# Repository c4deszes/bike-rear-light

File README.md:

# Rear Light

> An integrated tail, brake and turn signal light for bicycles.

## Gen 1

This generation is meant to demonstrate the tail light and brake light capabilities, turn signals
are not present.

The expected takeaways from it are:

- whether this simplified single PCB assembly is robust enough
- whether the amount of light produced is sufficient
- how certain lenses affect the optical qualities 
- what the thermals look like given the power consumption and enclosure with passive cooling
- whether this accelerometer is reliable to be used for the brake lights

Key findings:

- Accelerometer alone is not reliable for brake detection due to road vibrations. With filtering
  the reaction time goes up.
- Linear LED drivers are not efficient for the expected bus voltages, this is a problem for the
  continously on tail light
- Single LEDs spread out on a large area need lots of diffusing which reduces the light output

## Gen 1b

This generation is meant as a patch for the weak and uneven light output of Gen1. It's based on the
Gen1 front light hardware put inside a custom case.

There are no expectations.

Key findings:

- Mounting bracket broke during two incidents in an unservicable way

## Gen 2

This generation is meant to merge the good parts of Gen1 and Gen1b and improve a couple of things.
The main new feature is the included radar and the primary improvements are increased operational
voltage range and additional monitoring.

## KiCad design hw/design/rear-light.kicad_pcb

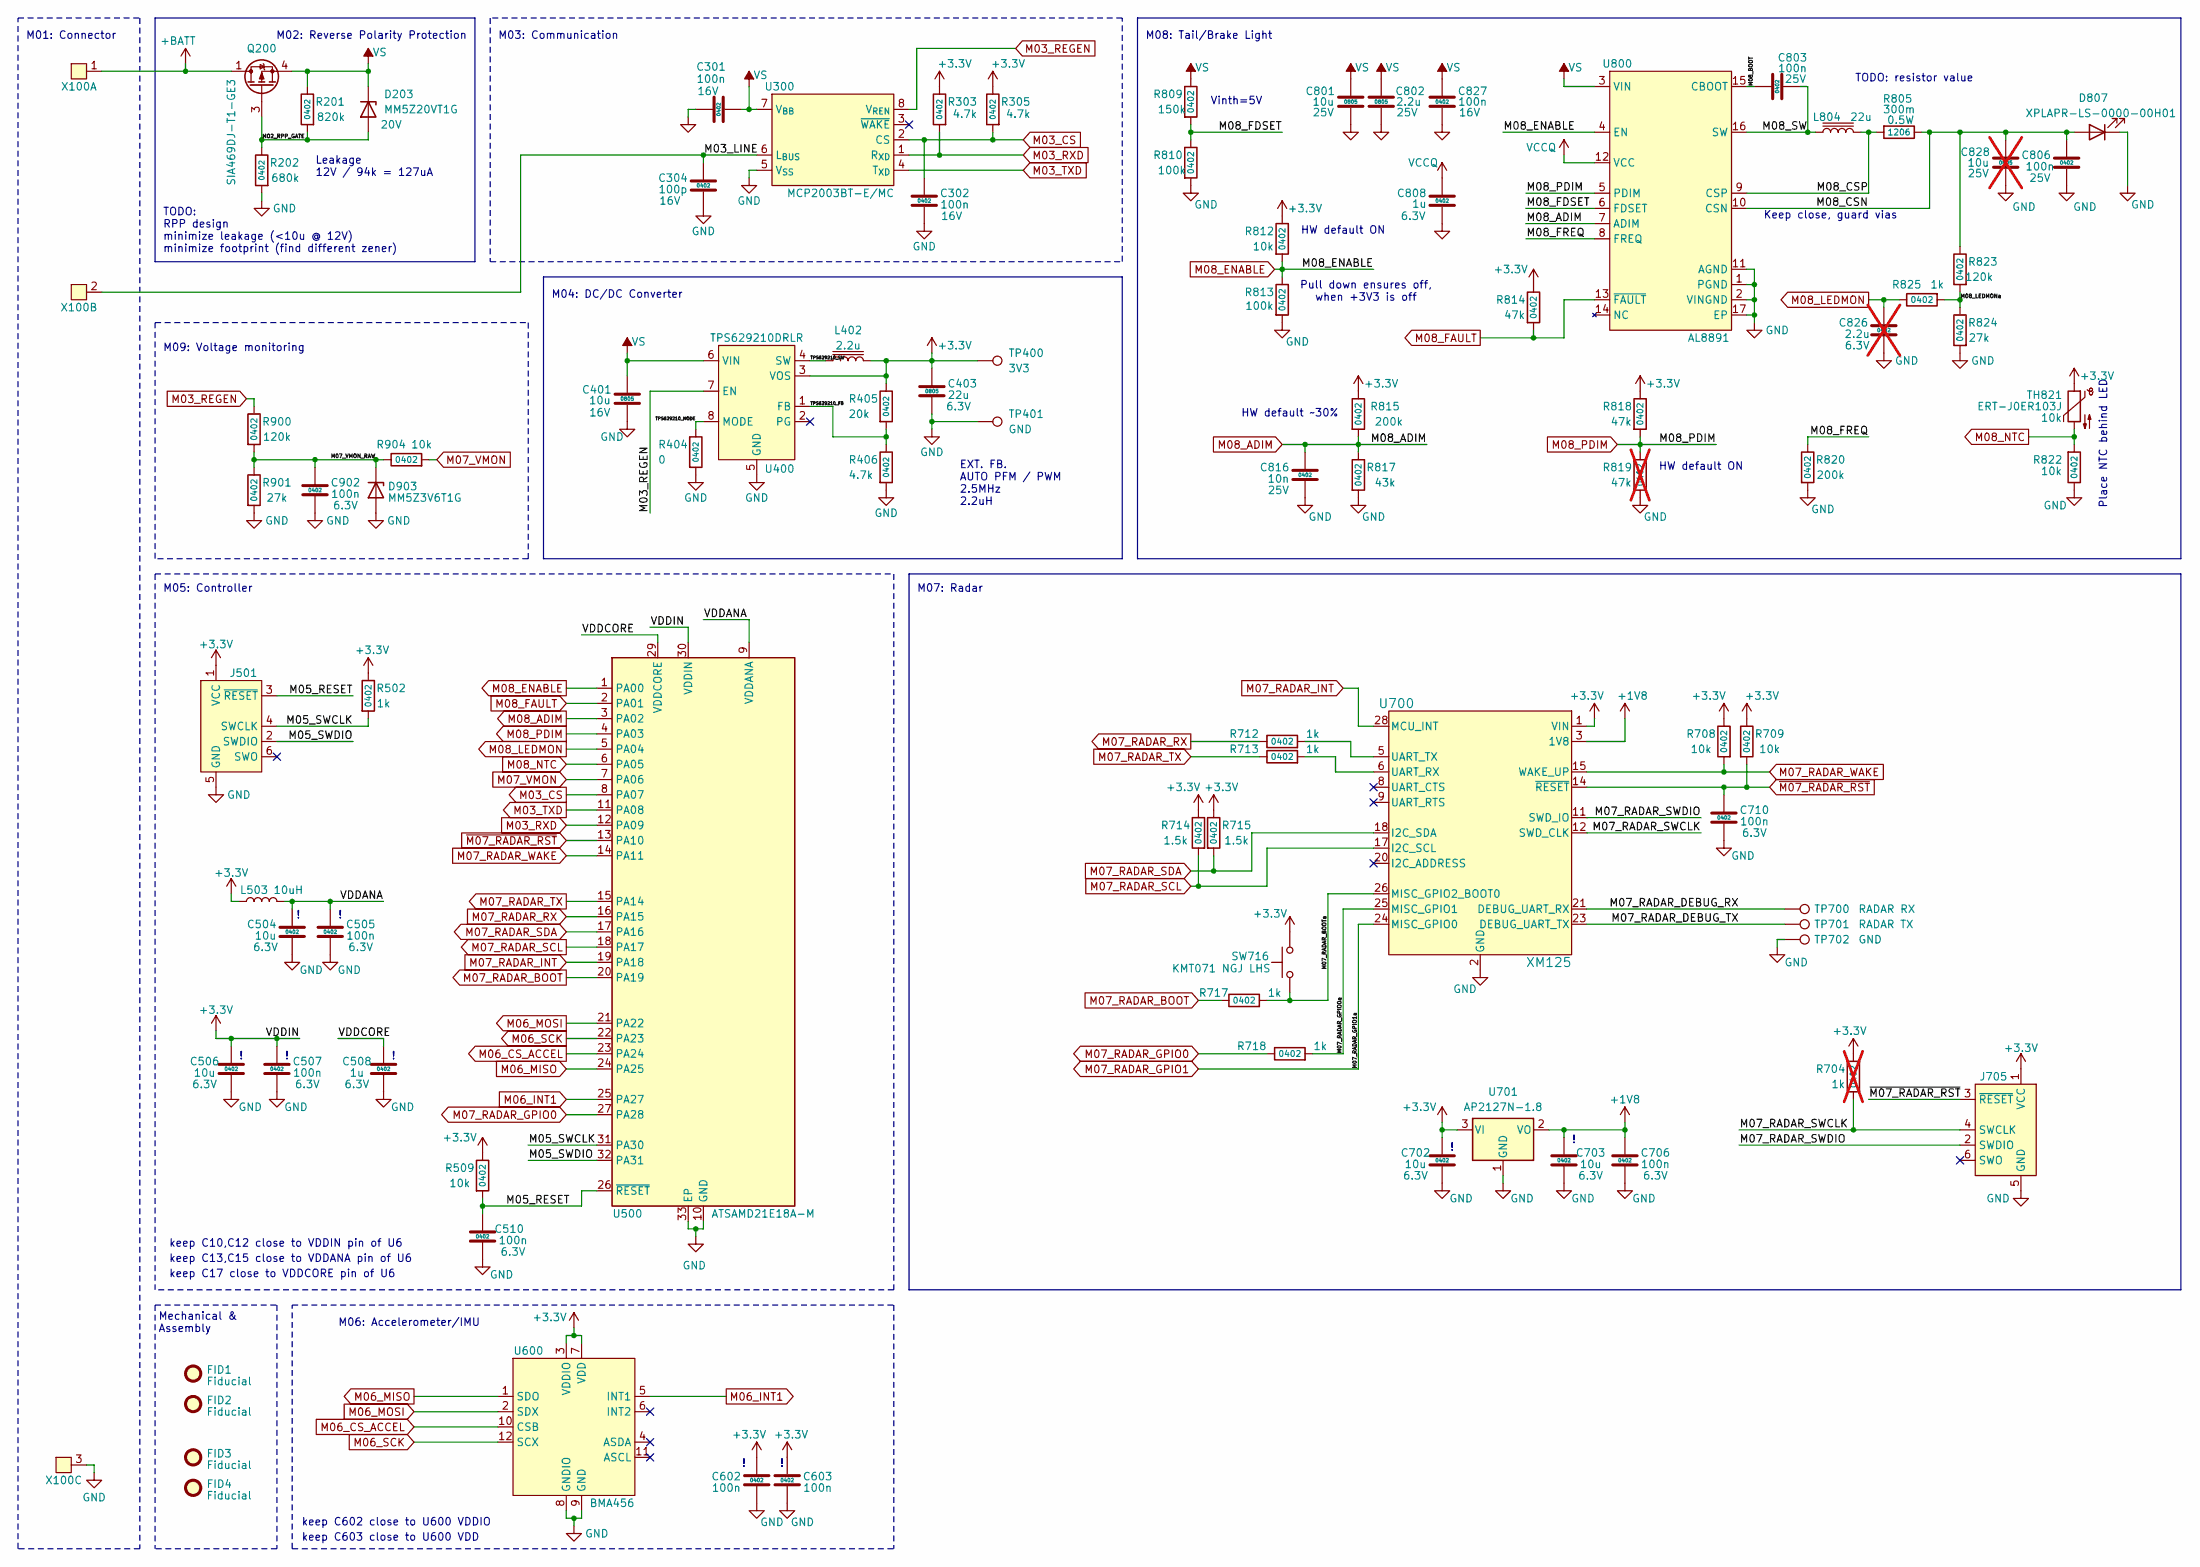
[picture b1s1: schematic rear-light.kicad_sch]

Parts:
C301, C302, C827: 100n; C_0402_1005Metric; Rating 16V
C304: 100p; C_0402_1005Metric; Rating 16V
C401: 10u; C_0805_2012Metric; Rating 16V
C403: 22u; C_0805_2012Metric; Rating 6.3V
C504, C506, C702, C703: 10u; C_0402_1005Metric; Rating 6.3V
C505, C507, C510, C706, C710, C902: 100n; C_0402_1005Metric; Rating 6.3V
C508, C808: 1u; C_0402_1005Metric; Rating 6.3V
C602, C603: 100n; C_0402_1005Metric
C801: 10u; C_0805_2012Metric; Rating 25V
C802: 2.2u; C_0805_2012Metric; Rating 25V
C803: 100n; C_0603_1608Metric; Rating 25V
C806: 100n; C_0402_1005Metric; Rating 25V
C816: 10n; C_0402_1005Metric; Rating 25V
C826: 2.2u; C_0402_1005Metric; Rating 6.3V; not fitted
C828: 10u; C_0805_2012Metric; Rating 25V; not fitted
D203: MM5Z20VT1G; D_SOD-523; Rating 20V
D807: XPLAPR-LS-0000-00H01; LED_Cree-XP
D903: MM5Z3V6T1G; D_SOD-523
FID1, FID2, FID3, FID4: Fiducial; Fiducial_0.5mm_Mask1mm
J501, J705: Conn_ARM_SWD_TagConnect_TC2030-NL; Tag-Connect_TC2030-IDC-NL_2x03_P1.27mm_Vertical
L402: 2.2u; L_Coilcraft_LPS3010
L503: 10uH; L_0603_1608Metric
L804: 22u; ASPI-6045
Q200: SIA469DJ-T1-GE3; Vishay_PowerPAK_SC70-6L_Single
R201: 820k; R_0402_1005Metric
R202: 680k; R_0402_1005Metric
R303, R305, R406: 4.7k; R_0402_1005Metric
R404: 0; R_0402_1005Metric
R405: 20k; R_0402_1005Metric
R502, R712, R713, R717, R718, R825: 1k; R_0402_1005Metric
R509, R708, R709, R812, R822, R904: 10k; R_0402_1005Metric
R704: 1k; R_0402_1005Metric; not fitted
R714, R715: 1.5k; R_0402_1005Metric
R805: 300m; R_1206_3216Metric; Rating 0.5W
R809: 150k; R_0402_1005Metric
R810, R813: 100k; R_0402_1005Metric
R814, R818: 47k; R_0402_1005Metric
R815, R820: 200k; R_0402_1005Metric
R817: 43k; R_0402_1005Metric
R819: 47k; R_0402_1005Metric; not fitted
R823, R900: 120k; R_0402_1005Metric
R824, R901: 27k; R_0402_1005Metric
SW716: KMT071 NGJ LHS; KMT0
TH821: ERT-J0ER103J; R_0402_1005Metric
TP400: 3V3; TestPoint_Pad_D1.0mm
TP401, TP702: GND; TestPoint_Pad_D1.0mm
TP700: RADAR RX; TestPoint_Pad_D1.0mm
TP701: RADAR TX; TestPoint_Pad_D1.0mm
U300: MCP2003BT-E/MC; DFN-8-1EP_3x2mm_P0.5mm_EP1.7x1.4mm
U400: TPS629210DRLR; SOT-583-8
U500: ATSAMD21E18A-M; QFN-32-1EP_5x5mm_P0.5mm_EP3.6x3.6mm
U600: BMA456; LGA-12_2x2mm_P0.5mm
U700: XM125; XM125_ACC-M
U701: AP2127N-1.8; SOT-23
U800: AL8891; TSSOP-16-1EP_4.4x5mm_P0.65mm_EP3x3mm
X100: JST_JWPF_B03B-JWPF-SK-R_1x03_P2.00mm_Vertical

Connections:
+1V8: C703.2, C706.2, U700.3 (1V8), U701.2 (VO)
+3.3V: C403.1, C506.2, C507.2, C602.2, C603.1, C702.2, J501.1 (VCC), J705.1 (VCC), L402.2, L503.1, R303.1, R305.1, R405.1, R502.1, R509.1, R704.1, R708.1, R709.1, R714.1, R715.1, R812.1, R814.1, R815.1, R818.1, SW716.2, TH821.1, TP400.1, U400.3 (VOS), U500.30 (VDDIN), U600.3 (VDDIO), U600.7 (VDD), U700.1 (VIN), U701.3 (VI)
+BATT: Q200.1 (D), X100.1
/M02_RPP_GATE: D203.2 (A), Q200.3 (G), R201.2, R202.1
/M03_LINE: C304.2, U300.6 (L_{BUS}), X100.2
/M05_RESET: C510.2, J501.3 (~RESET), R509.2, U500.26 (~RESET)
/M05_SWCLK: J501.4 (SWCLK), R502.2, U500.31 (PA30)
/M05_SWDIO: J501.2 (SWDIO), U500.32 (PA31)
/M07_RADAR_BOOTa: R717.2, SW716.1, U700.26 (MISC_GPIO2_BOOT0)
/M07_RADAR_DEBUG_RX: TP700.1, U700.21 (DEBUG_UART_RX)
/M07_RADAR_DEBUG_TX: TP701.1, U700.23 (DEBUG_UART_TX)
/M07_RADAR_GPIO0a: R718.2, U700.25 (MISC_GPIO1)
/M07_RADAR_SWCLK: J705.4 (SWCLK), R704.2, U700.12 (SWD_CLK)
/M07_RADAR_SWDIO: J705.2 (SWDIO), U700.11 (SWD_IO)
/M07_VMON_RAW: C902.2, D903.1 (K), R900.2, R901.1, R904.1
/M08_BOOT: C803.1, U800.15 (CBOOT)
/M08_CSN: C806.1, C828.2, D807.2 (A), R805.1, R823.1, U800.10 (CSN)
/M08_CSP: L804.2, R805.2, U800.9 (CSP)
/M08_FDSET: R809.2, R810.1, U800.6 (FDSET)
/M08_FREQ: R820.1, U800.8 (FREQ)
/M08_LEDMONa: R823.2, R824.1, R825.2
/M08_SW: C803.2, L804.1, U800.16 (SW)
/TPS629210_FB: R405.2, R406.1, U400.1 (FB)
/TPS629210_MODE: R404.1, U400.8 (MODE)
/TPS629210_SW: L402.1, U400.4 (SW)
/VDDANA: C504.2, C505.2, L503.2, U500.9 (VDDANA)
/VDDCORE: C508.2, U500.29 (VDDCORE)
GND: C301.1, C302.1, C304.1, C401.1, C403.2, C504.1, C505.1, C506.1, C507.1, C508.1, C510.1, C602.1, C603.2, C702.1, C703.1, C706.1, C710.1, C801.1, C802.1, C806.2, C808.1, C816.2, C826.1, C827.1, C828.1, C902.1, D807.1 (K), D903.2 (A), J501.5 (GND), J705.5 (GND), R202.2, R404.2, R406.2, R810.2, R813.2, R817.2, R819.2, R820.2, R822.1, R824.2, R901.2, TP401.1, TP702.1, U300.5 (V_{SS}), U400.5 (GND), U500.10 (GND), U500.28 (GND), U500.33 (EP), U600.8 (GNDIO), U600.9 (GND), U700.2 (GND), U700.4 (GND), U700.7 (GND), U700.10 (GND), U700.13 (GND), U700.16 (GND), U700.19 (GND), U700.22 (GND), U700.27 (GND), U701.1 (GND), U800.1 (PGND), U800.2 (VINGND), U800.11 (AGND), U800.17 (EP), X100.3
M03_CS: C302.2, R305.2, U300.2 (CS), U500.8 (PA07)
M03_REGEN: R900.1, U300.8 (V_{REN}), U400.7 (EN)
M03_RXD: R303.2, U300.1 (R_{XD}), U500.12 (PA09)
M03_TXD: U300.4 (T_{XD}), U500.11 (PA08)
M06_CS_ACCEL: U500.23 (PA24), U600.10 (CSB)
M06_INT1: U500.25 (PA27), U600.5 (INT1)
M06_MISO: U500.24 (PA25), U600.1 (SDO)
M06_MOSI: U500.21 (PA22), U600.2 (SDX)
M06_SCK: U500.22 (PA23), U600.12 (SCX)
M07_RADAR_BOOT: R717.1, U500.20 (PA19)
M07_RADAR_GPIO0: R718.1, U500.27 (PA28)
M07_RADAR_GPIO1: U700.24 (MISC_GPIO0)
M07_RADAR_INT: U500.19 (PA18), U700.28 (MCU_INT)
M07_RADAR_RX: R712.1, U500.16 (PA15)
M07_RADAR_SCL: R714.2, U500.18 (PA17), U700.17 (I2C_SCL)
M07_RADAR_SDA: R715.2, U500.17 (PA16), U700.18 (I2C_SDA)
M07_RADAR_TX: R713.1, U500.15 (PA14)
M07_RADAR_WAKE: R708.2, U500.14 (PA11), U700.15 (WAKE_UP)
M07_VMON: R904.2, U500.7 (PA06)
M08_ADIM: C816.1, R815.2, R817.1, U500.3 (PA02), U800.7 (ADIM)
M08_ENABLE: R812.2, R813.1, U500.1 (PA00), U800.4 (EN)
M08_FAULT: R814.2, U500.2 (PA01), U800.13 (~FAULT)
M08_LEDMON: C826.2, R825.1, U500.5 (PA04)
M08_NTC: R822.2, TH821.2, U500.6 (PA05)
M08_PDIM: R818.2, R819.1, U500.4 (PA03), U800.5 (PDIM)
unnamed: R713.2, U700.6 (UART_RX)
unnamed: R712.2, U700.5 (UART_TX)
VCCQ: C808.2, U800.12 (VCC)
VS: C301.2, C401.2, C801.2, C802.2, C827.2, D203.1 (K), Q200.4 (S), R201.1, R809.1, U300.7 (V_{BB}), U400.6 (VIN), U800.3 (VIN)
~M07_RADAR_RST: C710.2, J705.3 (~RESET), R709.2, U500.13 (PA10), U700.14 (~RESET)

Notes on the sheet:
M01: Connector
M04: DC/DC Converter
keep C17 close to VDDCORE pin of U6
M05: Controller
HW default ON
keep C13,C15 close to VDDANA pin of U6
Pull down ensures off, when +3V3 is off
EXT. FB. AUTO PFM / PWM 2.5MHz 2.2uH
M08: Tail/Brake Light
M06: Accelerometer/IMU
keep C10,C12 close to VDDIN pin of U6
M07: Radar
M02: Reverse Polarity Protection
keep C602 close to U600 VDDIO
Mechanical & Assembly
HW default ~30%
TODO: resistor value
M03: Communication
TODO: RPP design minimize leakage (<10u @ 12V) minimize footprint (find different zener)
M09: Voltage monitoring
Leakage 12V / 94k = 127uA
Vinth=5V
keep C603 close to U600 VDD
Keep close, guard vias
Place NTC behind LED

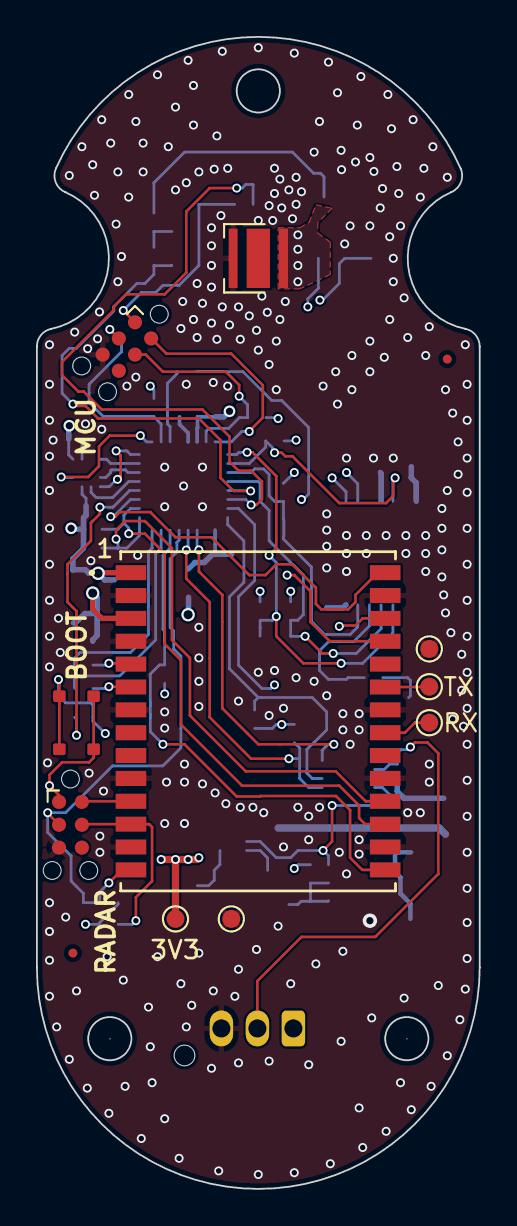
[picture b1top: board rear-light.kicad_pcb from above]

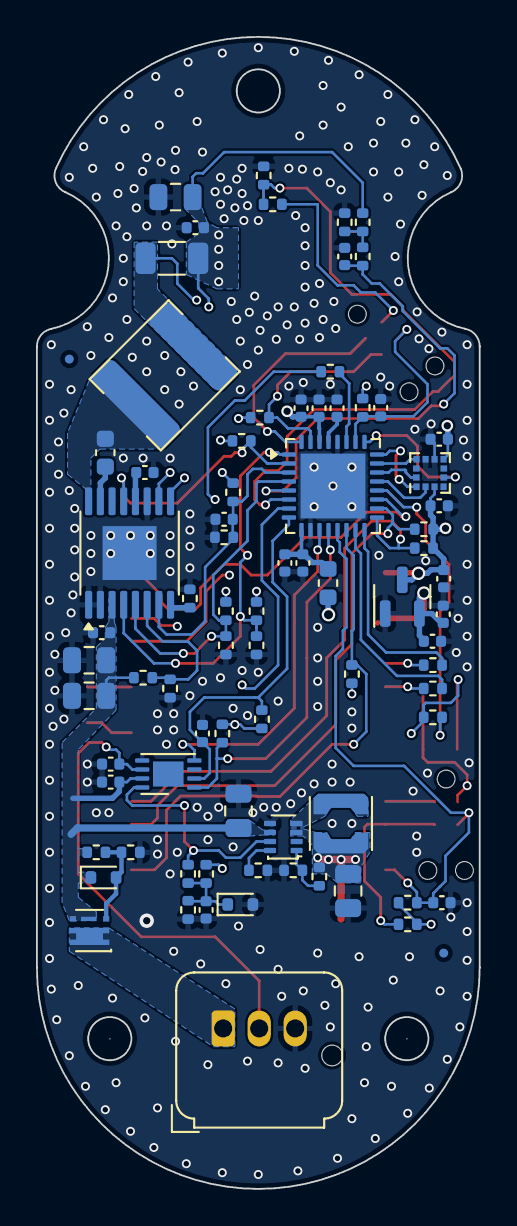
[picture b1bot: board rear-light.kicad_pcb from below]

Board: 4 copper layers, 24.6 x 64.0 mm, 91 parts (79 on the bottom side), 57 nets.

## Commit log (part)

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2024-02-06 Initial system requirements, arch, design
2024-03-10 Updated system design
2024-03-13 Updated system requirements
2024-03-13 Mechanical design Gen1.0
2024-03-14 Hardware design Gen1.0
2024-03-17 Adds hardware workflow
2024-03-17 drawio installation
2024-03-17 Fix CI
2024-03-24 Design updates
    Finalized schematic, layout is unchanged
2024-03-24 Gen1.0 design finalization (#1)
    * Final layout for Gen1.0, PCB has been ordered
    * Design documentation is mostly done
    * Schematic has been completed
2024-03-28 Software blinks brake and tail lights
2024-03-29 Blinking, but there's a delay
2024-03-29 Working blinking
2024-03-31 Safe
2024-03-31 System and brightness controller
2024-03-31 Safety blinking mode
2024-03-31 Rapid strobe and strobe interface rework
2024-04-02 Typo fix
2024-04-13 Working accelerometer data polling
2024-04-14 Working signal handling
    - System state transitions are working
    - Strobe config is used
    - Boot request support
2024-04-14 Network spec. update
2024-04-14 Support for safety mode
2024-04-19 Fixes
    LIN CS pin is set high to support transmission
    Boot entry support
    Updated strobe config
    Updated brightness curve
    Reacts to external brake signal
2024-04-19 Updated UART and SPI drivers
2024-04-19 Working new TCC driver
2024-04-20 Debug signals Adding light diagnostics Increase flash area
2024-04-20 Working diagnostic runs
2024-04-21 Self diagnosis faster and on all segments
2024-04-23 Fixed bootloader
2024-08-02 Tail light diagnostics working
2024-08-03 New brightness settings
    Safety mode no longer blinks
    Disabled diagnostics
    Deep sleep function
2024-08-03 Software design documentation
2024-08-04 Parameter documentation Version number is dynamic
2024-08-04 Network descriptor update
    Accelerometer error code is returned
    Code cleanup
2024-08-04 Shutdown support
2024-08-04 Latest LINE protocol version
2024-08-04 SW Release 1.0.0 finalization
2024-08-04 Workflow
2024-08-04 Task update
2024-08-04 Changed directory
2024-08-05 Codegen fixes
2024-08-05 Fix url
2024-08-05 User mode?
2024-08-05 Gen1.0 Initial software (#2)
    * Software blinks brake and tail lights
    * System and brightness controller
    * Safety blinking mode
    * Rapid strobe and strobe interface rework
    * Working accelerometer data polling
    * Working signal handling
2024-08-19 Working light control
2024-08-30 Working UDS properties
2024-08-30 Pin UDS version
2024-10-14 Gen1b mechanical parts
2024-10-14 New brightness configurations
2024-11-17 New bootloader and HAL integration
2024-11-24 Internal brake signal (disabled)
    Fixes fill at end of AppROM
    Updates electronics system version
2024-11-24 Latest bootloader version
2024-11-24 Bootloader and HAL update (#3)
    * New bootloader and HAL integration
    * Internal brake signal (disabled)
    * Updates electronics system version
2024-11-24 Uploading datasheets
    Changes 220n capacitors to 100n
    PWMI pull downs populated according to expected default behavior
2024-11-24 Uploading datasheets (#4)
    Changes 220n capacitors to 100n
    PWMI pull downs populated according to expected default behavior
2025-02-19 Initial design Schematic is mostly complete
2025-03-02 Integrated UDS profile
2025-03-30 Flash tool reintegration
2025-07-10 Test cases
2025-10-22 Gen1.0b mechanical design
    This is a design based on front light gen1.0 hardware, includes
    a mount.
2025-10-22 Gen1.0b mechanical design (#5)
    This is a design based on front light gen1.0 hardware, includes
    a mount.
2026-02-10 Restructuring components
    Fixes schedule timer not having power
    Fixes missing transition from safety to normal mode
    Reintroduced braking component, sensor can be disabled
    Accelerometer is initialized at board level
    LINE protocol interface pushed down to board level to aid SIL
    Updating LINE and UDS libs to latest version
2026-02-10 Updating bootloader
2026-02-10 SIL target creation Tooling reconfigured to ATSAMD21 target Updated to latest customer spec.
2026-02-10 Latest customer spec.
2026-02-20 Big rework
    INIT: changed loading sequence
    TASKS: changed task allocation
    VOLT: draft of voltage measurement
    SYSSTATE: config loading
    TEMP: draft of temperature measurement
    CURRENT: draft of current estimator
2026-02-24 Working TTADC, support for all 3 board versions
2026-02-27 Updated lightcontrol interface and TLD509x driver
2026-02-27 Fixes analog modulation at 0 brightness Fixes PWM modulation build
2026-05-04 Gen2.0 redesign - DCDC converter for LVIO - Voltage monitoring - Reverse polarity protection is P-FET - MCP2003 as LIN trans. - AL8891 LED driver - XM125 radar
2026-05-10 Finalized design
2026-05-10 IO allocation
2026-05-10 Turn signal design for reference
2026-05-10 Fabrication
2026-05-21 Finalization (JLC ordered)
2026-05-23 Support for different hardware generations
2026-05-24 Calibration, wake manager, systick
2026-06-05 Working configuration and diagnostics
2026-06-07 Compiling all board variants
2026-06-08 New default config for each board Calibration can be saved
2026-06-09 Reworked safety and emergency brightness use
2026-06-14 State machine refactor, added emergency mode
2026-06-14 Updated Gen2 default config
2026-06-14 Initial working XM125 integration It just reads the version every 100ms
2026-06-14 Compiling XM125 code
2026-06-18 Minimal working radar
2026-06-20 Basic radar operation (disabled for now)
2026-06-20 Radar precompiled examples
2026-06-20 Devcontainer includes STM32 dev pack
2026-06-21 All generations build
2026-06-21 Config auto reload, disabling internal braking for now
2026-06-21 Fix calibration saving
2026-06-21 Move diag speed limit to feature control
2026-06-21 Disabling emergency entry at low voltage
2026-06-21 Fix for Gen1x not having Uart interrupt handler
